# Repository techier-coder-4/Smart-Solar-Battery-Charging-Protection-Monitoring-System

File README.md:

Schematic:

PCB Layout: 

3D View:

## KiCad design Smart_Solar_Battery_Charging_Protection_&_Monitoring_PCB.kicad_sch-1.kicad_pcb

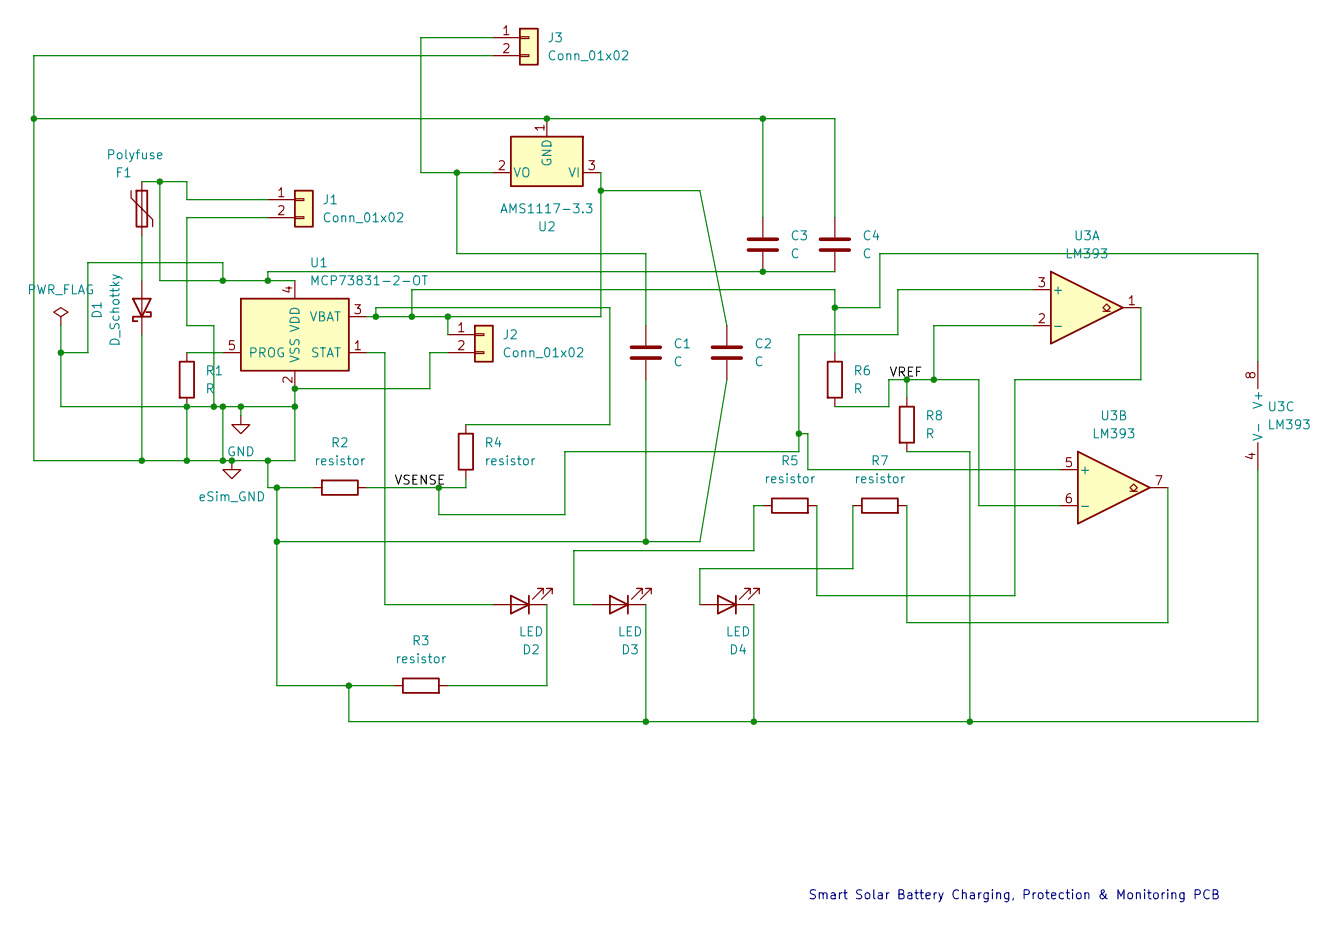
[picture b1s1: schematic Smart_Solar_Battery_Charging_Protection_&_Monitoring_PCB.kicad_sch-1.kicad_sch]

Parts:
C1, C2, C3, C4: C; C_Disc_D5.0mm_W2.5mm_P5.00mm
D1: D_Schottky; D_A-405_P7.62mm_Horizontal
D2, D3, D4: LED; LED_D5.0mm_Horizontal_O6.35mm_Z3.0mm
F1: Polyfuse; Fuse_BelFuse_0ZRE0075FF_L11.5mm_W4.8mm
J1, J2, J3: Conn_01x02; PhoenixContact_MSTB_2,5_2-GF-5,08_1x02_P5.08mm_Horizontal_T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
R1, R6, R8: R; R_Axial_DIN0207_L6.3mm_D2.5mm_P7.62mm_Horizontal
R2, R3, R4, R5, R7: resistor; R_Axial_DIN0207_L6.3mm_D2.5mm_P7.62mm_Horizontal
U1: MCP73831-2-OT; SOT-23-5
U2: AMS1117-3.3; SOT-223-3_TabPin2
U3: LM393; SOIC-8_3.9x4.9mm_P1.27mm

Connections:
/VREF: R6.2, R8.1, U3.2 (-), U3.6 (-)
/VSENSE: R2.1, R4.1, U3.3 (+), U3.5 (+)
GND: C1.2, C2.2, C3.1, C3.2, C4.1, C4.2, D1.1 (K), D3.1 (K), D4.1 (K), F1.1, J1.1, J1.2, J2.2, J3.2, R1.2, R2.2, R3.1, R8.2, U1.2 (VSS), U1.4 (VDD), U2.1 (GND), U3.4 (V-)
unnamed: C1.1, J3.1, U2.2 (VO)
unnamed: C2.1, J2.1, R4.2, R6.1, U1.3 (VBAT), U2.3 (VI), U3.8 (V+)
unnamed: D1.2 (A), F1.2
unnamed: D2.1 (K), R3.2
unnamed: D2.2 (A), U1.1 (STAT)
unnamed: D3.2 (A), R5.1
unnamed: D4.2 (A), R7.1
unnamed: R1.1, U1.5 (PROG)
unnamed: R5.2, U3.1
unnamed: R7.2, U3.7

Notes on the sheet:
Smart Solar Battery Charging, Protection & Monitoring PCB

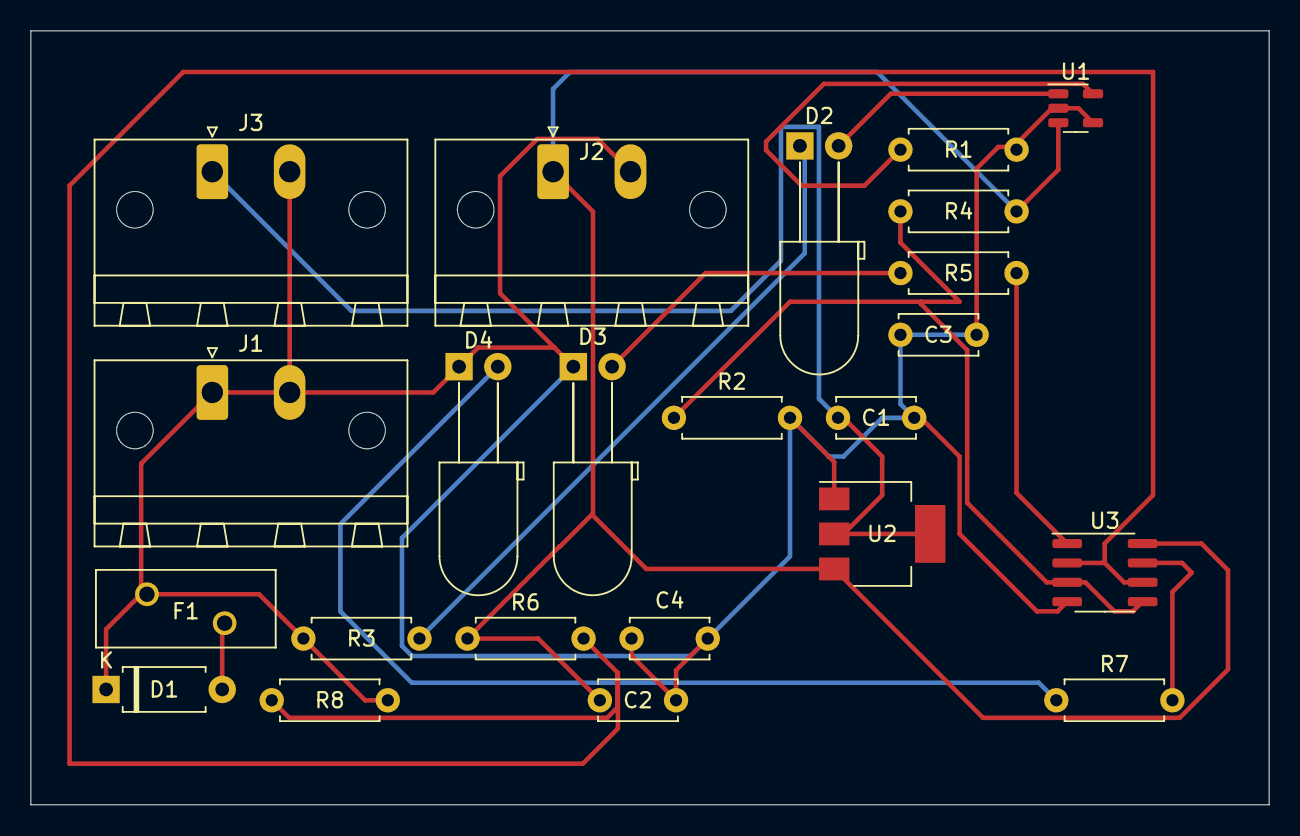
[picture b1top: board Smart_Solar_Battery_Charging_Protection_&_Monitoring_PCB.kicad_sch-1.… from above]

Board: 2 copper layers, 81.3 x 50.8 mm, 23 parts (0 on the bottom side), 13 nets.
